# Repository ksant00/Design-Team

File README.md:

# Overview
Projects done as part of design team - UBC Subbots.

## Technologies:
- Altium Designer
- KiCad
- Visal Studio Code
- Git
- Microcontrollers

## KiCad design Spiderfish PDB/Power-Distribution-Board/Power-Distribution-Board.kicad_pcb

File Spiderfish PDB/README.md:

# PDB
Power distribution PCB (100mm x 80mm)

Step down battery voltage (14.8 nominal) to 12V, 9V, 7V, and 5V with 15A current amapacity each. 

Microntroler (STM32) handles:
+ undervoltage and overcurrent protection faults from regulators
+ enable control from main computer via USB
+ watchdog for main computer (soft restart when main computer freezes)

# Schematic:

# Layout
Front:

Back:

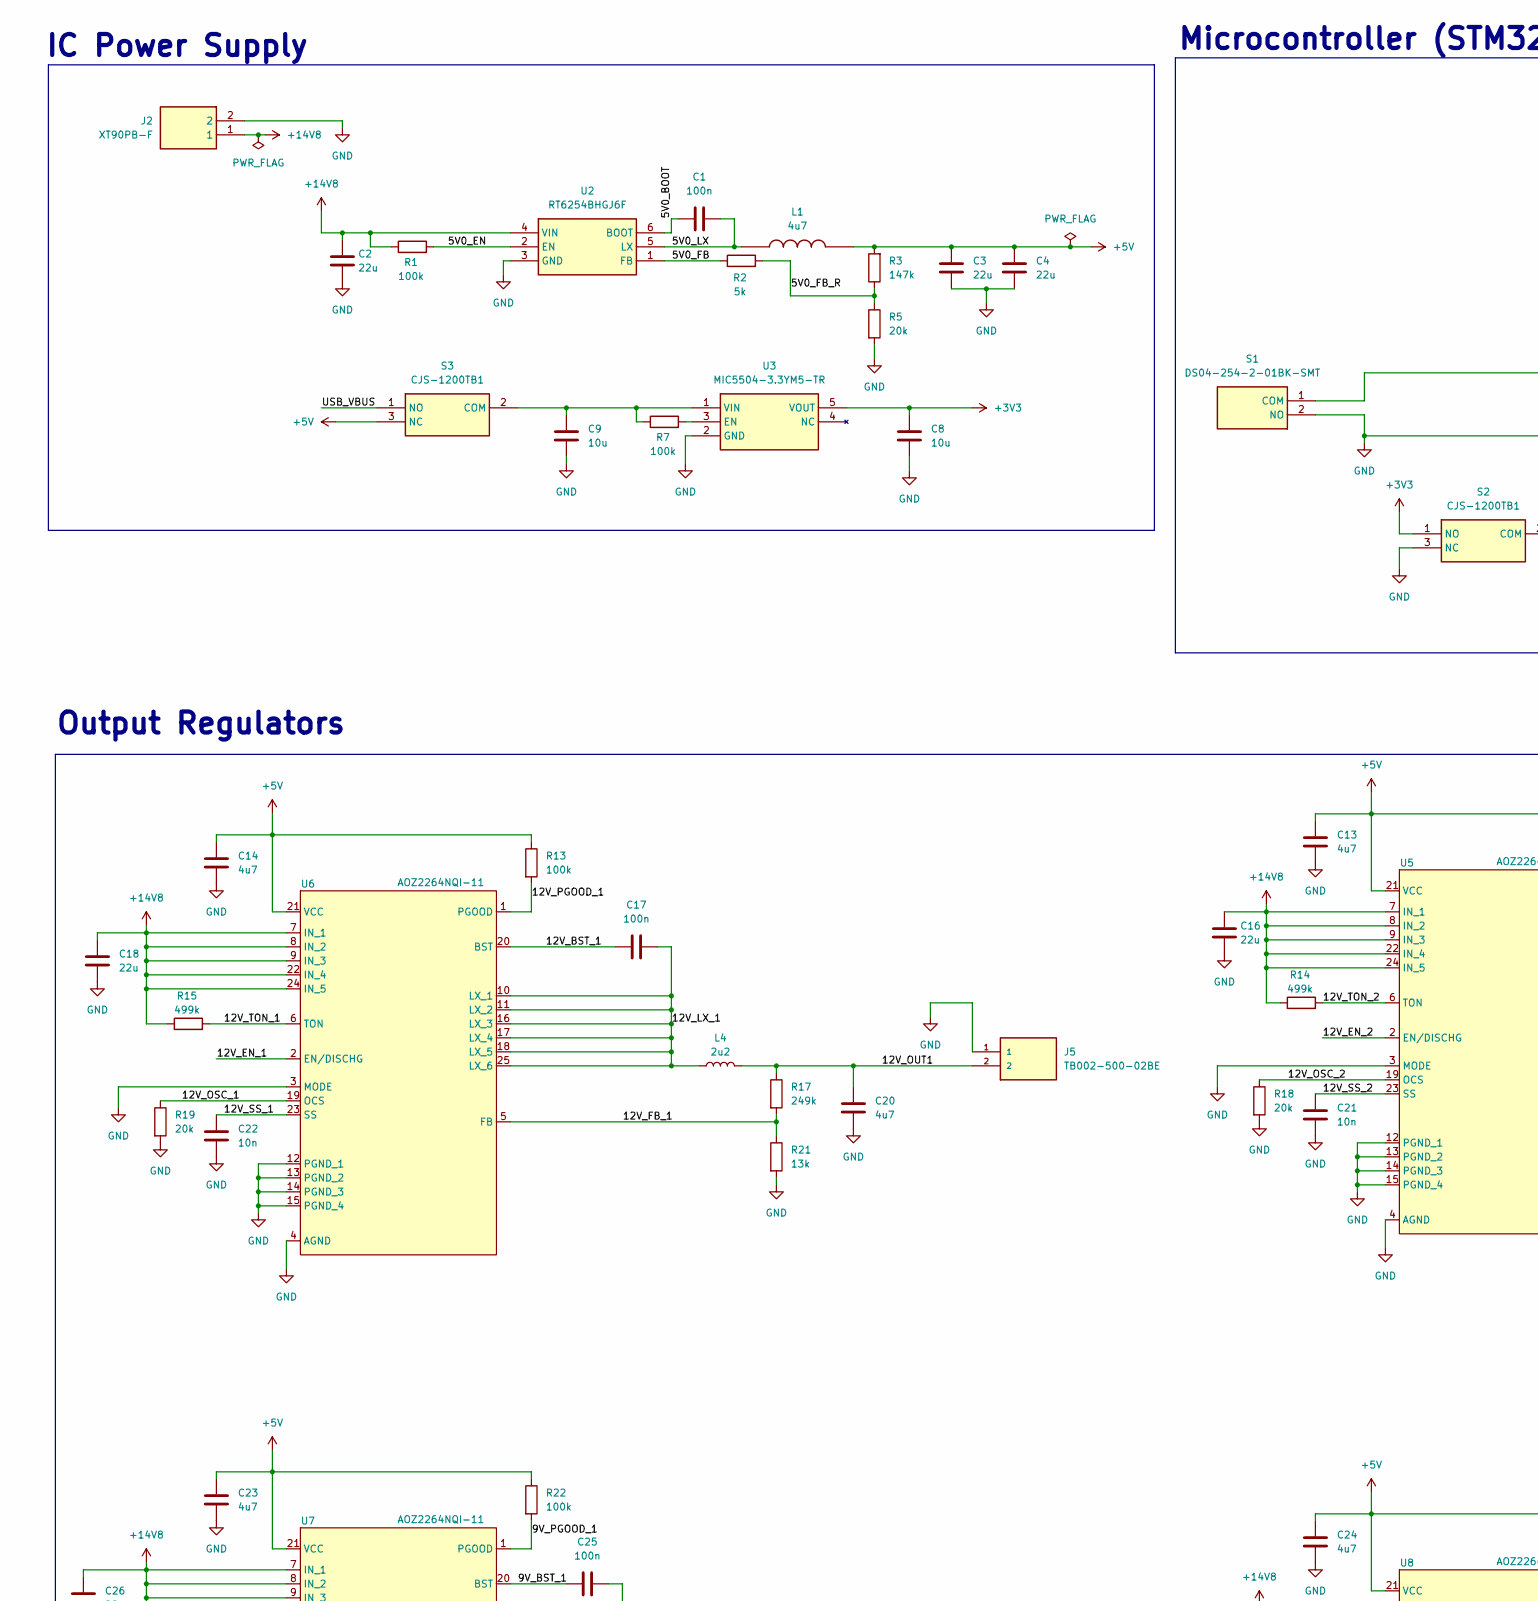
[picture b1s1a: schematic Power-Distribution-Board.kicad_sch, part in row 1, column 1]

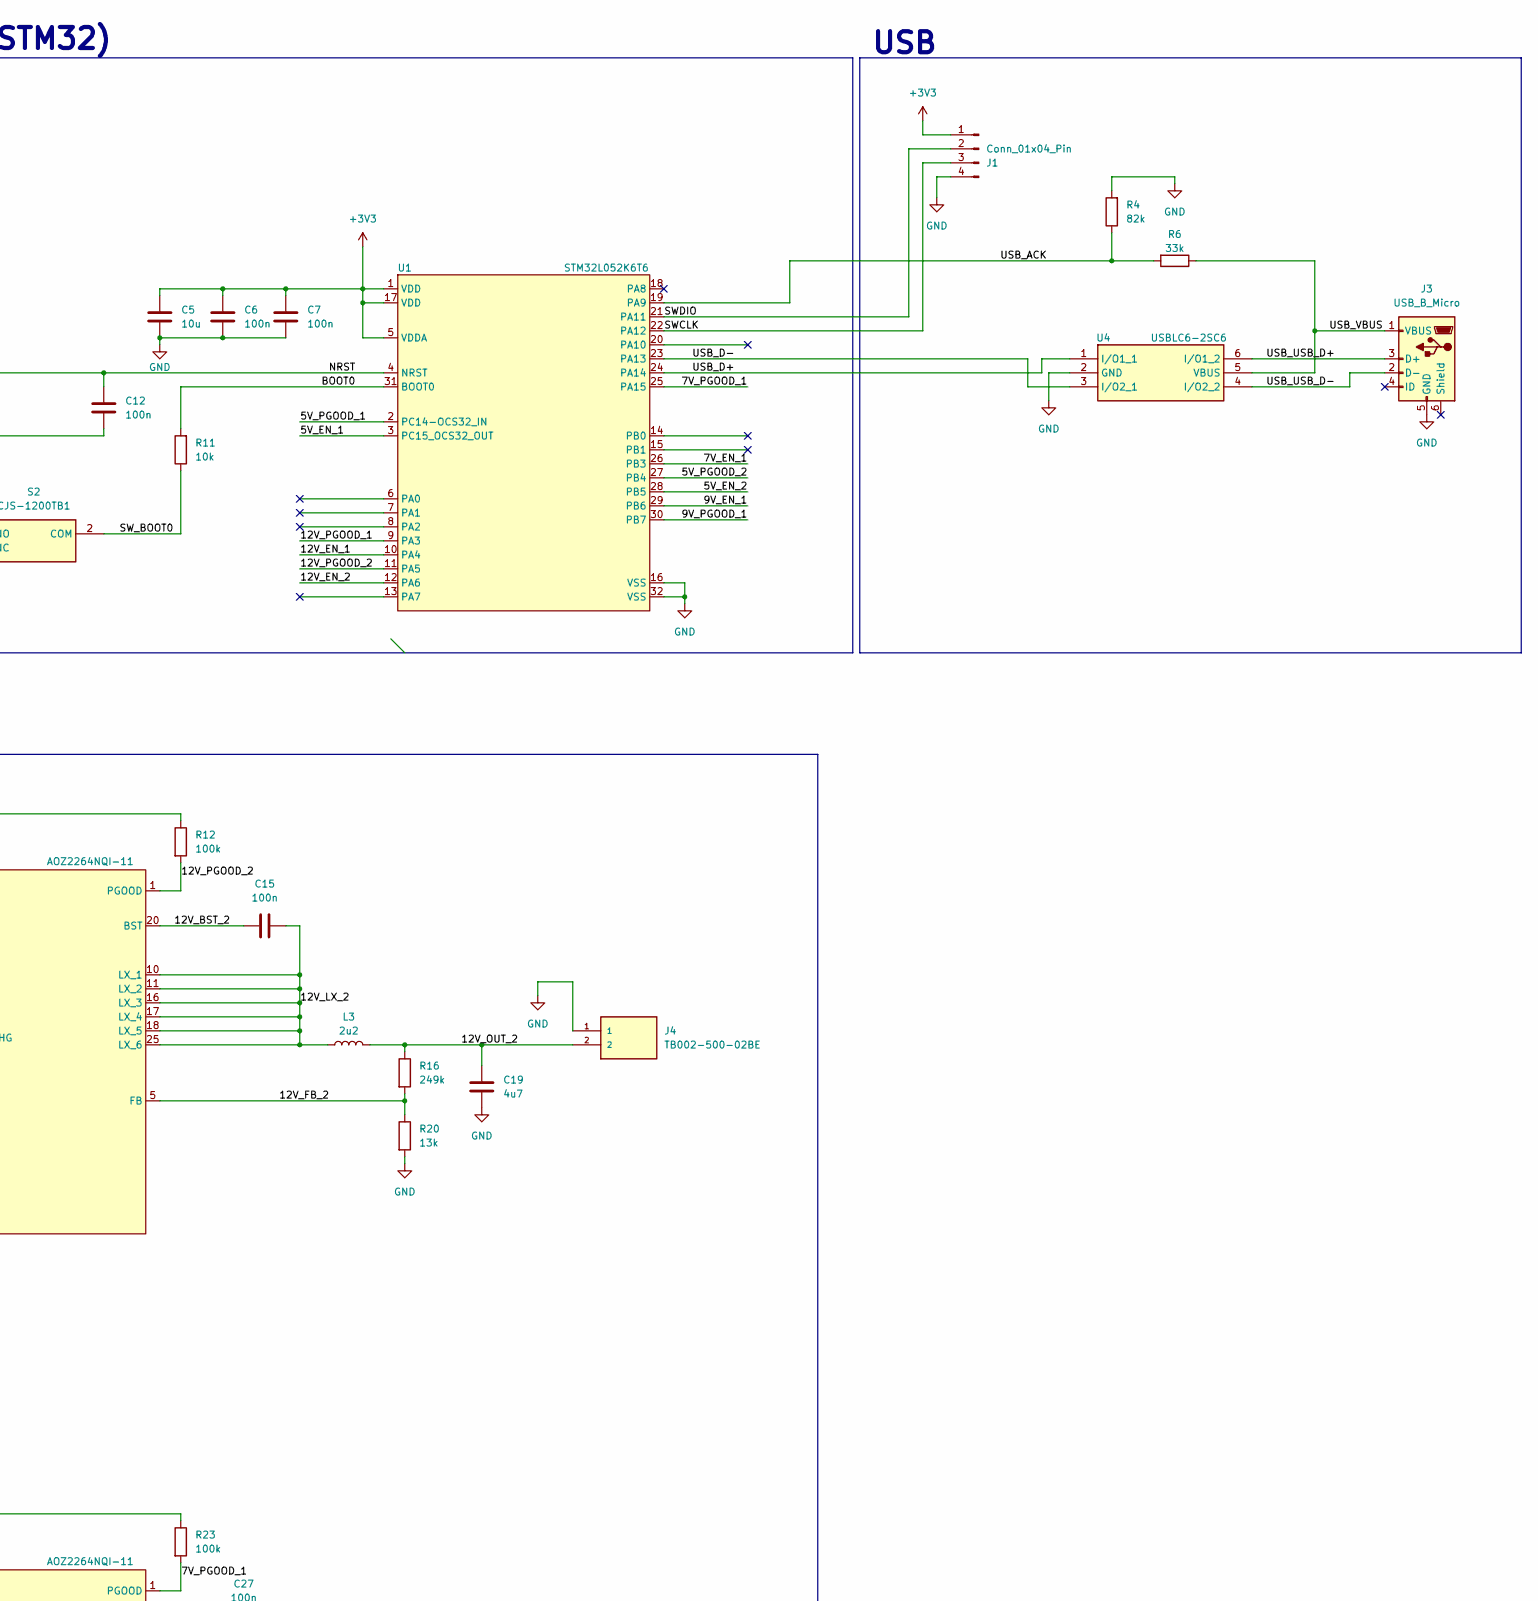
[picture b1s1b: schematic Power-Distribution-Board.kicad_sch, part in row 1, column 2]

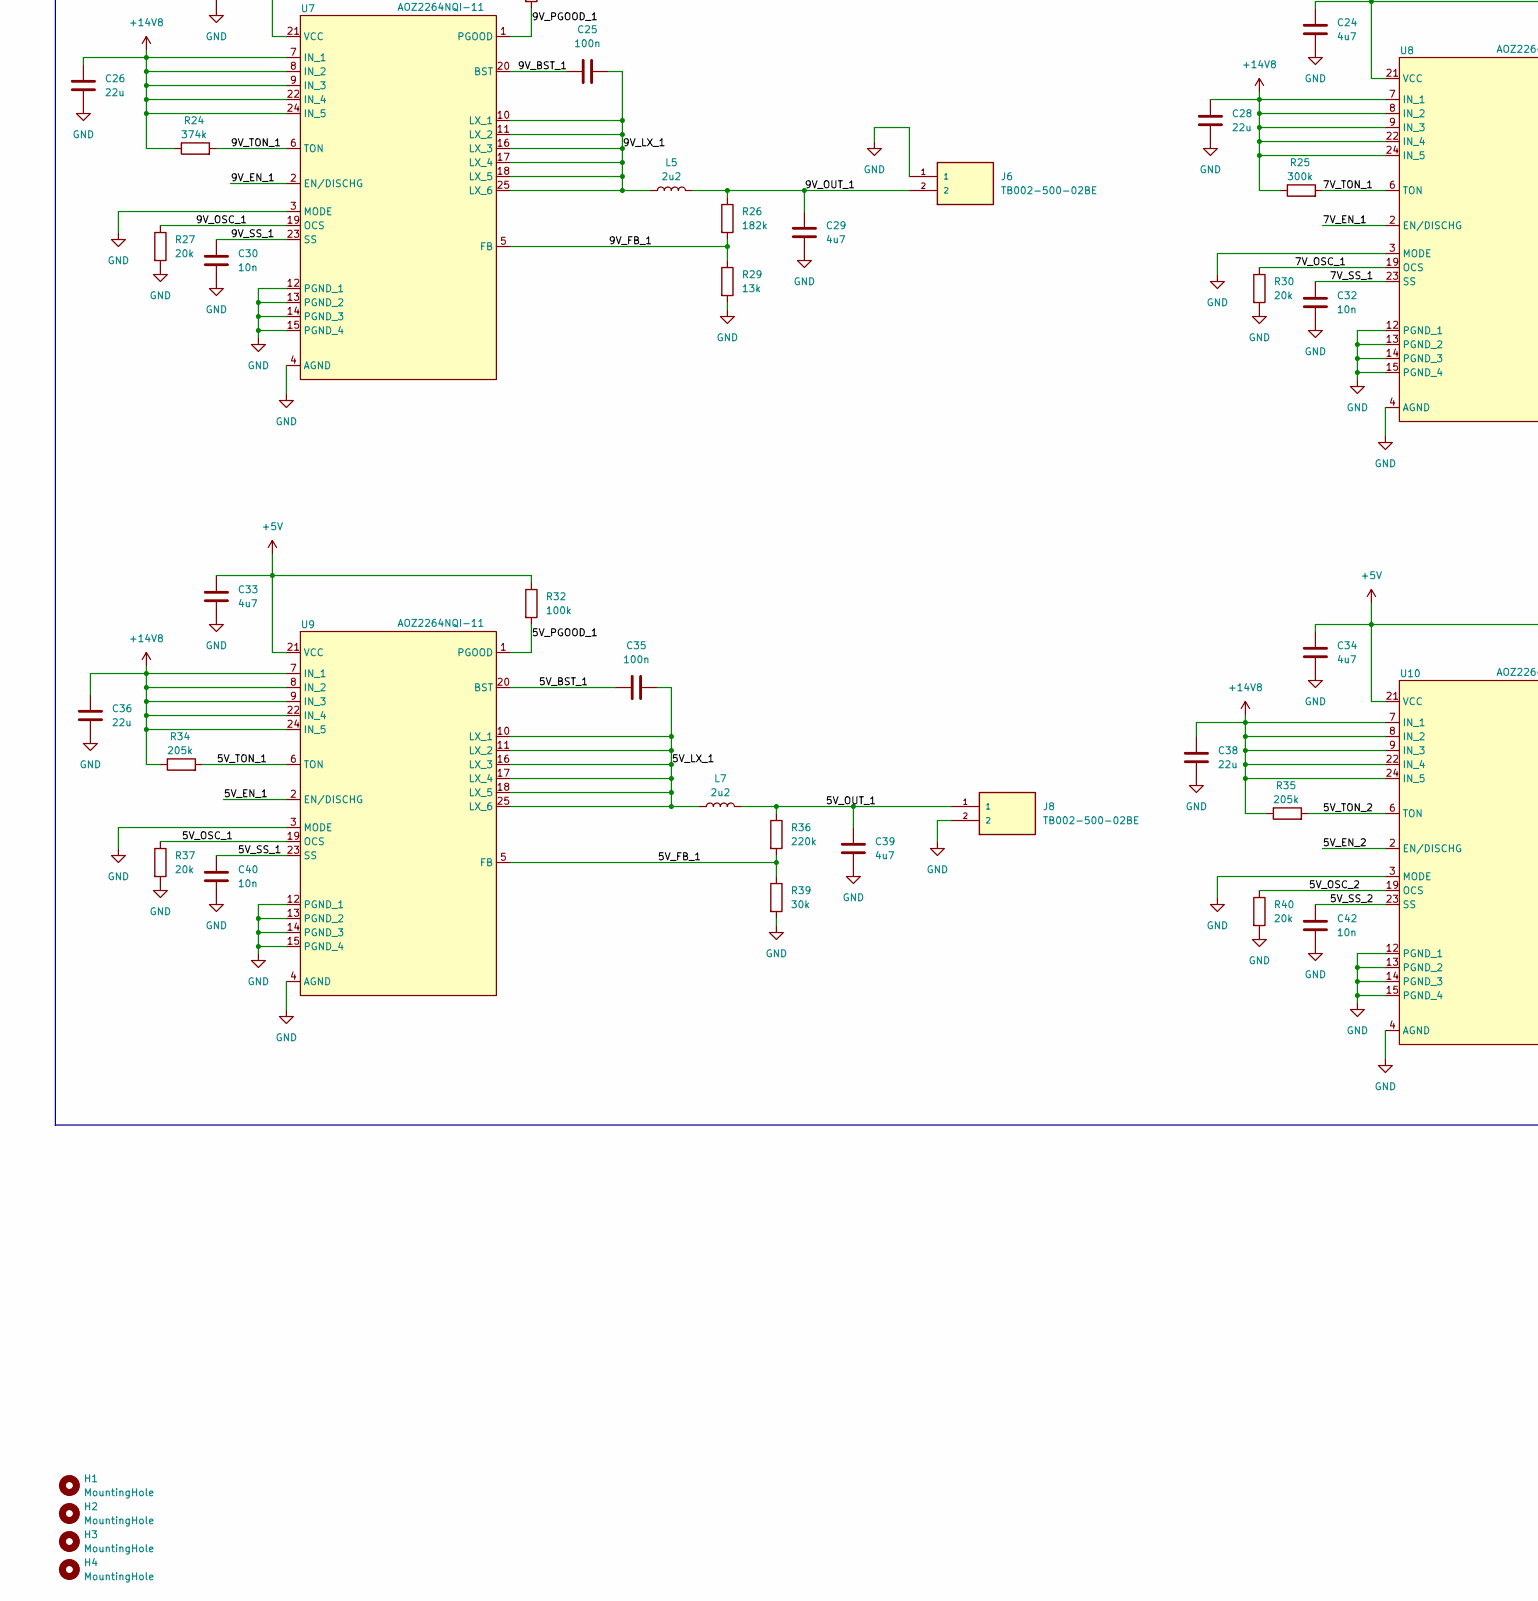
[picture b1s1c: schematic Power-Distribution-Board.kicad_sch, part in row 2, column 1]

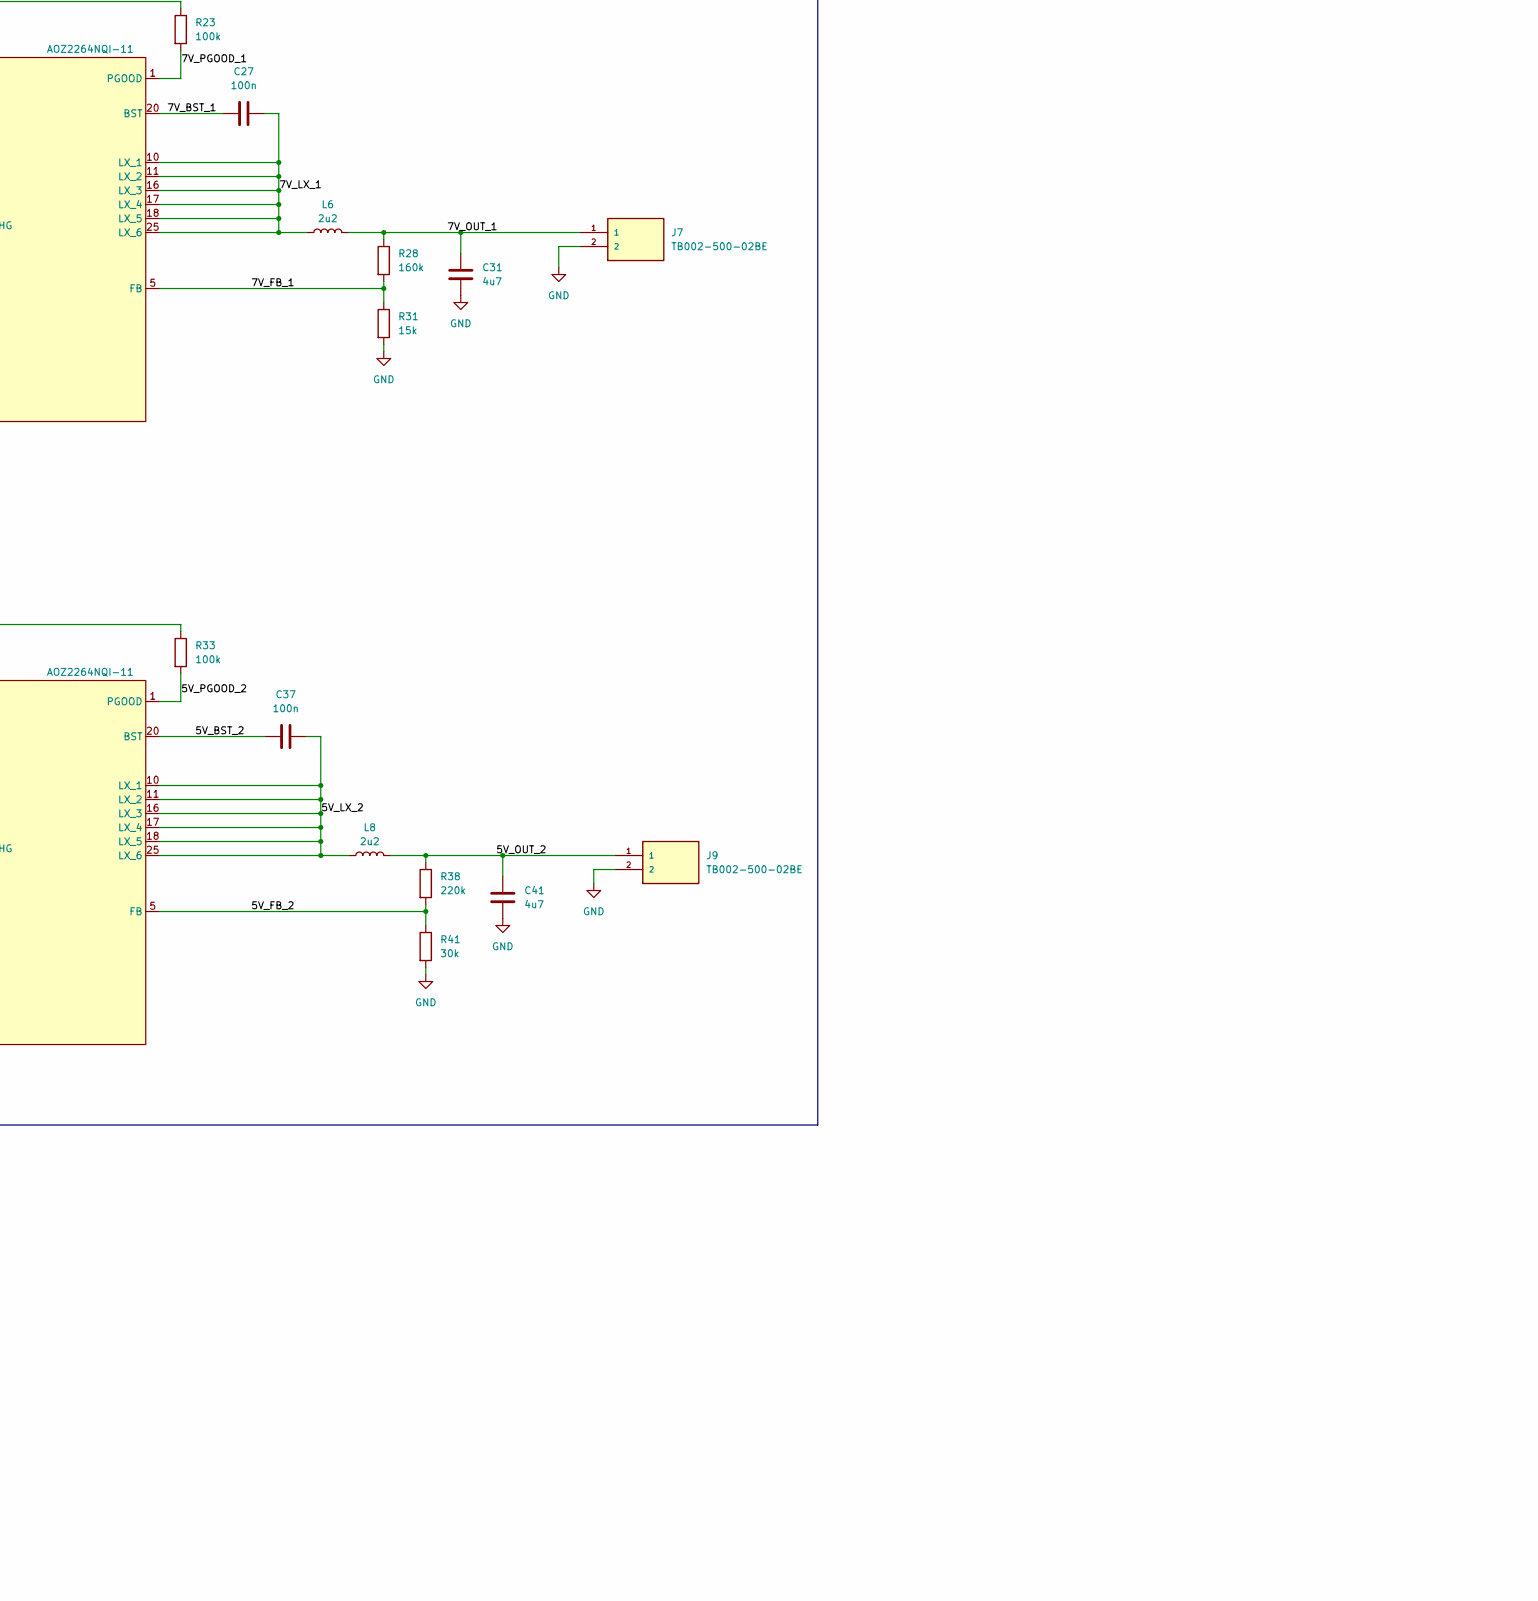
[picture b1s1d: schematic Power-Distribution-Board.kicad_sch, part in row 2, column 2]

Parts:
C1, C6, C7, C12, C15, C17, C25, C27, C35, C37: 100n; C_1206_3216Metric_Pad1.33x1.80mm_HandSolder
C2, C3, C4, C16, C18, C26, C28, C36, C38: 22u; C_0805_2012Metric_Pad1.18x1.45mm_HandSolder
C5, C8, C9: 10u; C_0805_2012Metric_Pad1.18x1.45mm_HandSolder
C13, C14, C19, C20, C23, C24, C29, C31, C33, C34, C39, C41: 4u7; C_0805_2012Metric_Pad1.18x1.45mm_HandSolder
C21, C22, C30, C32, C40, C42: 10n; C_0805_2012Metric_Pad1.18x1.45mm_HandSolder
H1, H2, H3, H4: MountingHole; MountingHole_3.2mm_M3_DIN965
J1: Conn_01x04_Pin; PinHeader_1x04_P2.54mm_Vertical
J2: XT90PB-F; XT90PBF
J3: USB_B_Micro; 629105150521
J4, J5, J6, J7, J8, J9: TB002-500-02BE
L1: 4u7; IHLP-4040DZ-01
L3, L4, L5, L6, L7, L8: 2u2; SRP1265A-2R2M
R1, R7, R12, R13, R22, R23, R32, R33: 100k; R_0603_1608Metric_Pad0.98x0.95mm_HandSolder
R2: 5k; R_0603_1608Metric_Pad0.98x0.95mm_HandSolder
R3: 147k; R_0603_1608Metric_Pad0.98x0.95mm_HandSolder
R4: 82k; R_0603_1608Metric_Pad0.98x0.95mm_HandSolder
R5, R18, R19, R27, R30, R37, R40: 20k; R_0603_1608Metric_Pad0.98x0.95mm_HandSolder
R6: 33k; R_0603_1608Metric_Pad0.98x0.95mm_HandSolder
R11: 10k; R_0603_1608Metric_Pad0.98x0.95mm_HandSolder
R14, R15: 499k; R_0603_1608Metric_Pad0.98x0.95mm_HandSolder
R16, R17: 249k; R_0603_1608Metric_Pad0.98x0.95mm_HandSolder
R20, R21, R29: 13k; R_0603_1608Metric_Pad0.98x0.95mm_HandSolder
R24: 374k; R_0603_1608Metric_Pad0.98x0.95mm_HandSolder
R25: 300k; R_0603_1608Metric_Pad0.98x0.95mm_HandSolder
R26: 182k; R_0603_1608Metric_Pad0.98x0.95mm_HandSolder
R28: 160k; R_0603_1608Metric_Pad0.98x0.95mm_HandSolder
R31: 15k; R_0603_1608Metric_Pad0.98x0.95mm_HandSolder
R34, R35: 205k; R_0603_1608Metric_Pad0.98x0.95mm_HandSolder
R36, R38: 220k; R_0603_1608Metric_Pad0.98x0.95mm_HandSolder
R39, R41: 30k; R_0603_1608Metric_Pad0.98x0.95mm_HandSolder
S1: DS04-254-2-01BK-SMT; DS04254201BKSMT
S2, S3: CJS-1200TB1; CJS1200TB1
U1: STM32L052K6T6
U2: RT6254BHGJ6F
U3: MIC5504-3.3YM5-TR
U4: USBLC6-2SC6; Manufacturer_Part_Number USBLC6-2SC6; Mouser Part Number 511-USBLC6-2SC6
U5, U6, U7, U8, U9, U10: AOZ2264NQI-11; AOZ2264NQI11

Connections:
+3V3: C5.1, C6.1, C7.1, C8.1, J1.1, S2.1 (NO), U1.1 (VDD), U1.5 (VDDA), U1.17 (VDD), U3.5 (VOUT)
+5V: C3.1, C4.1, C13.1, C14.1, C23.1, C24.1, C33.1, C34.1, L1.2, R3.2, R12.1, R13.1, R22.1, R23.1, R32.1, R33.1, S3.3 (NC), U5.21 (VCC), U6.21 (VCC), U7.21 (VCC), U8.21 (VCC), U9.21 (VCC), U10.21 (VCC)
+14V8: C2.1, C16.1, C18.1, C26.1, C28.1, C36.1, C38.1, J2.1, R1.1, R14.1, R15.1, R24.1, R25.1, R34.1, R35.1, U2.4 (VIN), U5.7 (IN_1), U5.8 (IN_2), U5.9 (IN_3), U5.22 (IN_4), U5.24 (IN_5), U6.7 (IN_1), U6.8 (IN_2), U6.9 (IN_3), U6.22 (IN_4), U6.24 (IN_5), U7.7 (IN_1), U7.8 (IN_2), U7.9 (IN_3), U7.22 (IN_4), U7.24 (IN_5), U8.7 (IN_1), U8.8 (IN_2), U8.9 (IN_3), U8.22 (IN_4), U8.24 (IN_5), U9.7 (IN_1), U9.8 (IN_2), U9.9 (IN_3), U9.22 (IN_4), U9.24 (IN_5), U10.7 (IN_1), U10.8 (IN_2), U10.9 (IN_3), U10.22 (IN_4), U10.24 (IN_5)
/5V0_BOOT: C1.1, U2.6 (BOOT)
/5V0_EN: R1.2, U2.2 (EN)
/5V0_FB: R2.1, U2.1 (FB)
/5V0_FB_R: R2.2, R3.1, R5.1
/5V0_LX: C1.2, L1.1, U2.5 (LX)
/5V_BST_1: C35.1, U9.20 (BST)
/5V_BST_2: C37.1, U10.20 (BST)
/5V_EN_1: U1.3 (PC15_OCS32_OUT), U9.2 (EN/DISCHG)
/5V_EN_2: U1.28 (PB5), U10.2 (EN/DISCHG)
/5V_FB_1: R36.2, R39.1, U9.5 (FB)
/5V_FB_2: R38.2, R41.1, U10.5 (FB)
/5V_LX_1: C35.2, L7.1, U9.10 (LX_1), U9.11 (LX_2), U9.16 (LX_3), U9.17 (LX_4), U9.18 (LX_5), U9.25 (LX_6)
/5V_LX_2: C37.2, L8.1, U10.10 (LX_1), U10.11 (LX_2), U10.16 (LX_3), U10.17 (LX_4), U10.18 (LX_5), U10.25 (LX_6)
/5V_OSC_1: R37.1, U9.19 (OCS)
/5V_OSC_2: R40.1, U10.19 (OCS)
/5V_OUT_1: C39.1, J8.1, L7.2, R36.1
/5V_OUT_2: C41.1, J9.1, L8.2, R38.1
/5V_PGOOD_1: R32.2, U1.2 (PC14-OCS32_IN), U9.1 (PGOOD)
/5V_PGOOD_2: R33.2, U1.27 (PB4), U10.1 (PGOOD)
/5V_SS_1: C40.1, U9.23 (SS)
/5V_SS_2: C42.1, U10.23 (SS)
/5V_TON_1: R34.2, U9.6 (TON)
/5V_TON_2: R35.2, U10.6 (TON)
/7V_BST_1: C27.1, U8.20 (BST)
/7V_EN_1: U1.26 (PB3), U8.2 (EN/DISCHG)
/7V_FB_1: R28.2, R31.1, U8.5 (FB)
/7V_LX_1: C27.2, L6.1, U8.10 (LX_1), U8.11 (LX_2), U8.16 (LX_3), U8.17 (LX_4), U8.18 (LX_5), U8.25 (LX_6)
/7V_OSC_1: R30.1, U8.19 (OCS)
/7V_OUT_1: C31.1, J7.1, L6.2, R28.1
/7V_PGOOD_1: R23.2, U1.25 (PA15), U8.1 (PGOOD)
/7V_SS_1: C32.1, U8.23 (SS)
/7V_TON_1: R25.2, U8.6 (TON)
/9V_BST_1: C25.1, U7.20 (BST)
/9V_EN_1: U1.29 (PB6), U7.2 (EN/DISCHG)
/9V_FB_1: R26.2, R29.1, U7.5 (FB)
/9V_LX_1: C25.2, L5.1, U7.10 (LX_1), U7.11 (LX_2), U7.16 (LX_3), U7.17 (LX_4), U7.18 (LX_5), U7.25 (LX_6)
/9V_OSC_1: R27.1, U7.19 (OCS)
/9V_OUT_1: C29.1, J6.2, L5.2, R26.1
/9V_PGOOD_1: R22.2, U1.30 (PB7), U7.1 (PGOOD)
/9V_SS_1: C30.1, U7.23 (SS)
/9V_TON_1: R24.2, U7.6 (TON)
/12V_BST_1: C17.1, U6.20 (BST)
/12V_BST_2: C15.1, U5.20 (BST)
/12V_EN_1: U1.10 (PA4), U6.2 (EN/DISCHG)
/12V_EN_2: U1.12 (PA6), U5.2 (EN/DISCHG)
/12V_FB_1: R17.2, R21.1, U6.5 (FB)
/12V_FB_2: R16.2, R20.1, U5.5 (FB)
/12V_LX_1: C17.2, L4.1, U6.10 (LX_1), U6.11 (LX_2), U6.16 (LX_3), U6.17 (LX_4), U6.18 (LX_5), U6.25 (LX_6)
/12V_LX_2: C15.2, L3.1, U5.10 (LX_1), U5.11 (LX_2), U5.16 (LX_3), U5.17 (LX_4), U5.18 (LX_5), U5.25 (LX_6)
/12V_OSC_1: R19.1, U6.19 (OCS)
/12V_OSC_2: R18.1, U5.19 (OCS)
/12V_OUT1: C20.1, J5.2, L4.2, R17.1
/12V_OUT_2: C19.1, J4.2, L3.2, R16.1
/12V_PGOOD_1: R13.2, U1.9 (PA3), U6.1 (PGOOD)
/12V_PGOOD_2: R12.2, U1.11 (PA5), U5.1 (PGOOD)
/12V_SS_1: C22.1, U6.23 (SS)
/12V_SS_2: C21.1, U5.23 (SS)
/12V_TON_1: R15.2, U6.6 (TON)
/12V_TON_2: R14.2, U5.6 (TON)
/BOOT0: R11.2, U1.31 (BOOT0)
/NRST: C12.1, S1.1 (COM), U1.4 (NRST)
/SWCLK: J1.3, U1.22 (PA12)
/SWDIO: J1.2, U1.21 (PA11)
/SW_BOOT0: R11.1, S2.2 (COM)
/USB_ACK: R4.1, R6.2, U1.19 (PA9)
/USB_D+: U1.24 (PA14), U4.1 (I/O1_1)
/USB_D-: U1.23 (PA13), U4.3 (I/O2_1)
/USB_USB_D+: J3.3 (D+), U4.6 (I/O1_2)
/USB_USB_D-: J3.2 (D-), U4.4 (I/O2_2)
/USB_VBUS: J3.1 (VBUS), R6.1, S3.1 (NO), U4.5 (VBUS)
GND: C2.2, C3.2, C4.2, C5.2, C6.2, C7.2, C8.2, C9.2, C12.2, C13.2, C14.2, C16.2, C18.2, C19.2, C20.2, C21.2, C22.2, C23.2, C24.2, C26.2, C28.2, C29.2, C30.2, C31.2, C32.2, C33.2, C34.2, C36.2, C38.2, C39.2, C40.2, C41.2, C42.2, J1.4, J2.2, J3.5 (GND), J4.1, J5.1, J6.1, J7.2, J8.2, J9.2, R4.2, R5.2, R18.2, R19.2, R20.2, R21.2, R27.2, R29.2, R30.2, R31.2, R37.2, R39.2, R40.2, R41.2, S1.2 (NO), S2.3 (NC), U1.16 (VSS), U1.32 (VSS), U2.3 (GND), U3.2 (GND), U4.2 (GND), U5.3 (MODE), U5.4 (AGND), U5.12 (PGND_1), U5.13 (PGND_2), U5.14 (PGND_3), U5.15 (PGND_4), U6.3 (MODE), U6.4 (AGND), U6.12 (PGND_1), U6.13 (PGND_2), U6.14 (PGND_3), U6.15 (PGND_4), U7.3 (MODE), U7.4 (AGND), U7.12 (PGND_1), U7.13 (PGND_2), U7.14 (PGND_3), U7.15 (PGND_4), U8.3 (MODE), U8.4 (AGND), U8.12 (PGND_1), U8.13 (PGND_2), U8.14 (PGND_3), U8.15 (PGND_4), U9.3 (MODE), U9.4 (AGND), U9.12 (PGND_1), U9.13 (PGND_2), U9.14 (PGND_3), U9.15 (PGND_4), U10.3 (MODE), U10.4 (AGND), U10.12 (PGND_1), U10.13 (PGND_2), U10.14 (PGND_3), U10.15 (PGND_4)
unnamed: C9.1, R7.1, S3.2 (COM), U3.1 (VIN)
unnamed: R7.2, U3.3 (EN)

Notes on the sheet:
Microcontroller (STM32)
USB
Output Regulators
IC Power Supply

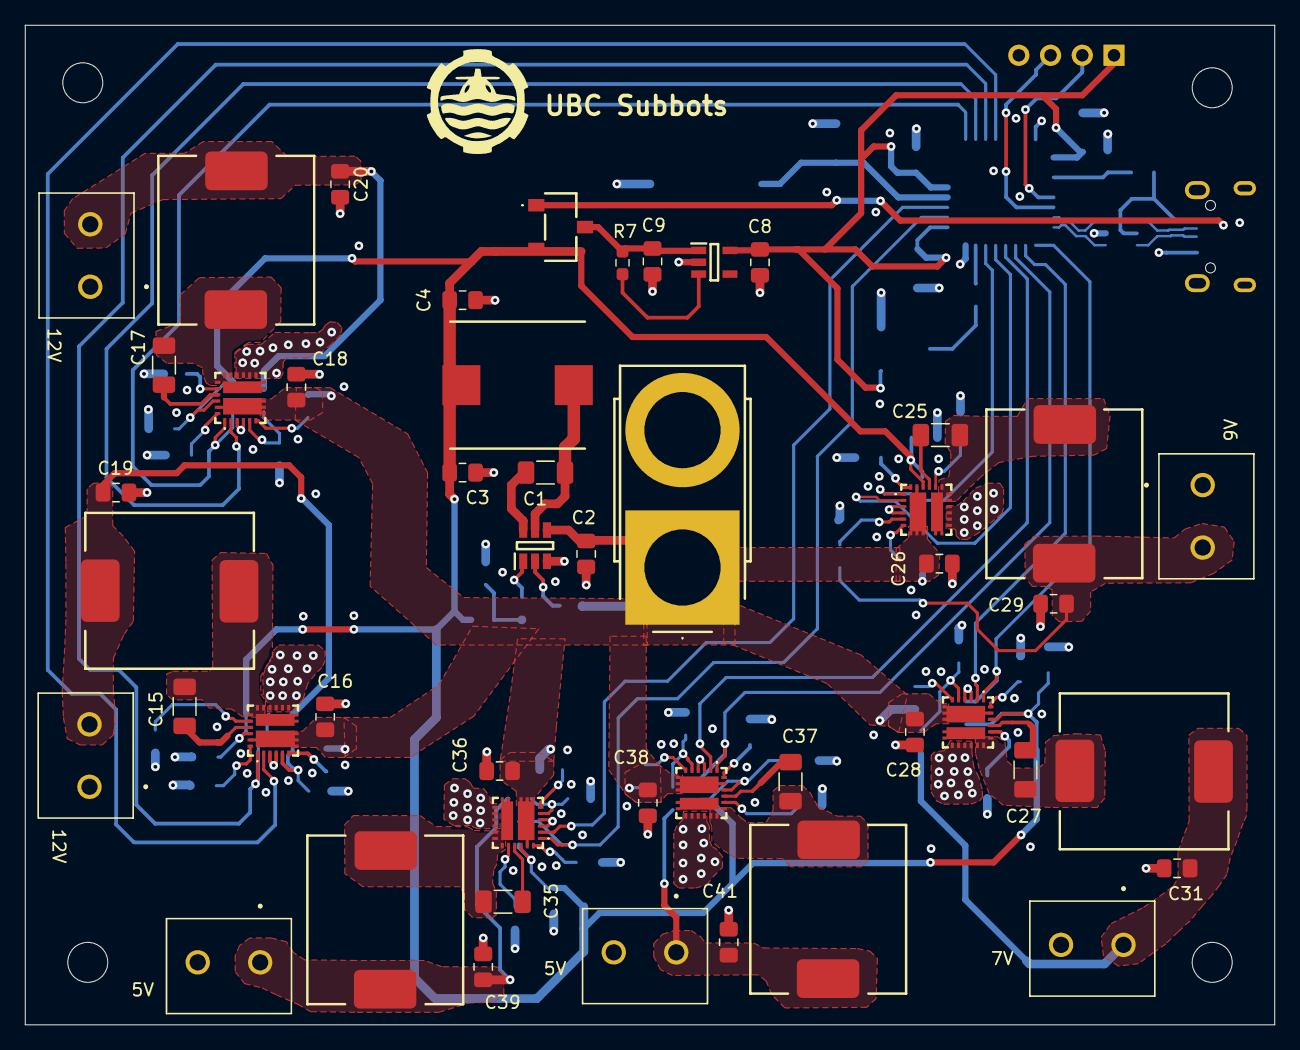
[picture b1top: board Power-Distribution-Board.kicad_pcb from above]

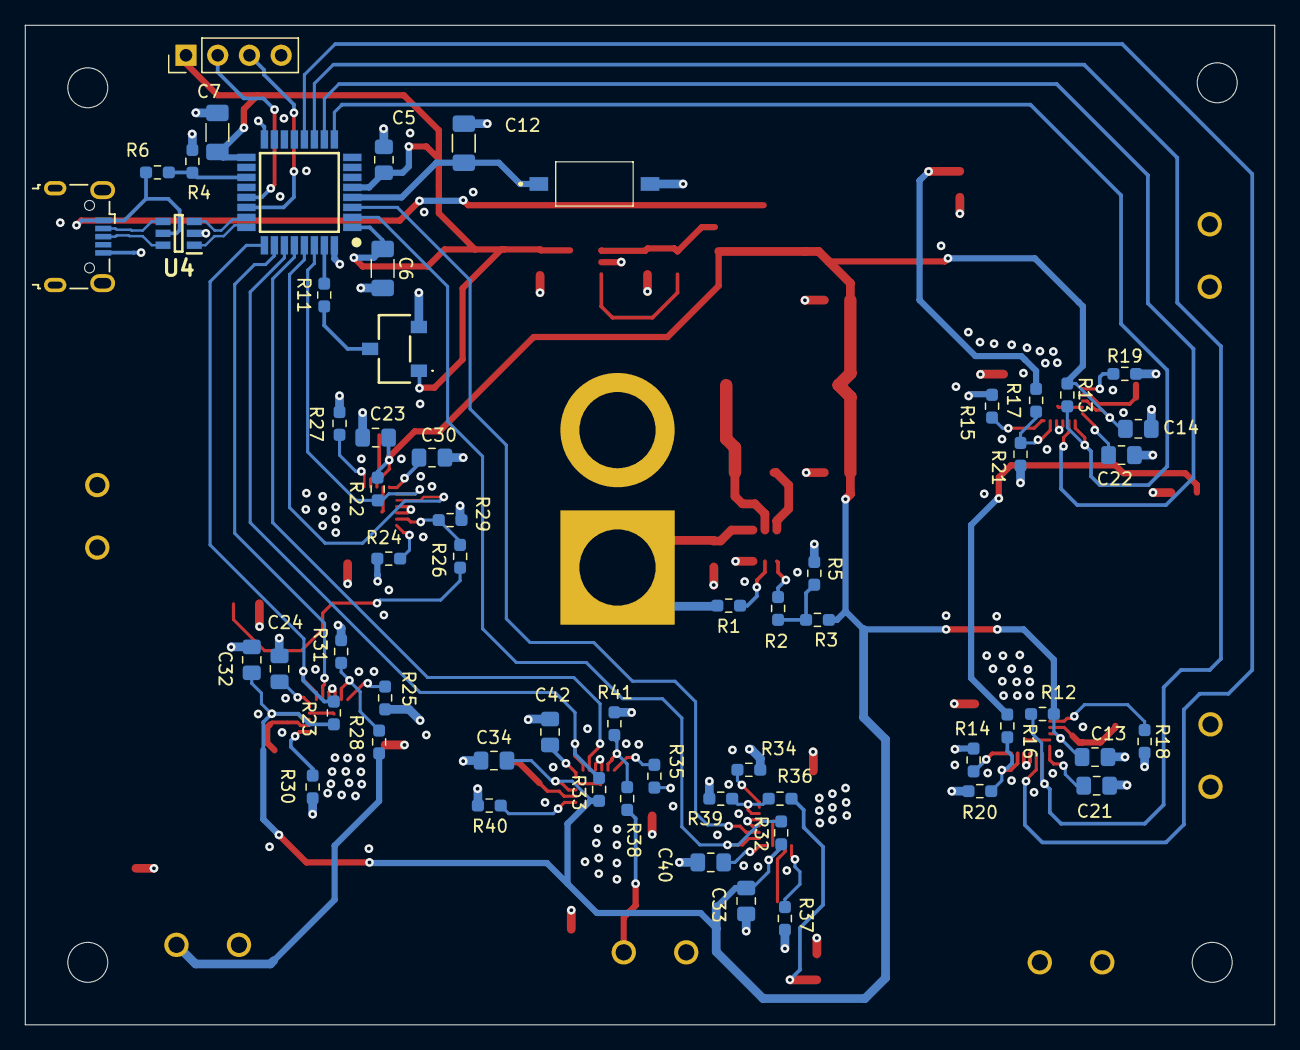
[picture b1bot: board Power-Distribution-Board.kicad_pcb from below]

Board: 4 copper layers, 100.0 x 80.0 mm, 111 parts (59 on the bottom side), 76 nets.

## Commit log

2025-06-10 uploaded files
2026-03-21 upload start
2026-03-21 added all regulators
2026-03-25 added footprints and p/n
2026-03-26 changed resistor package to 0603 from 0805
2026-03-27 added connectors
2026-03-28 added net labels
2026-03-28 finished adding labels and net classes
2026-03-28 added base design constraints and grouped pcb components
2026-03-28 rough layout for 12V reg and mcu
2026-03-29 rough layout
2026-03-30 changed mcu and ic regulator model and refined output regulator layout
2026-03-30 refined layout
2026-04-02 rough laytout for all regs, need to increase board size to 10x10
2026-04-04 Revision A - changed 3.3V regulator to LDO - all routing done - component selection done
    to do:
    - update silkscreen placment
    - stitching vias
2026-04-06 updated silkscreen placement + usb power switch
2026-04-06 cleaned up schematic + readme
